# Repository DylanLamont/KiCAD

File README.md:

# KiCAD
Repo to save KiCAD Projects

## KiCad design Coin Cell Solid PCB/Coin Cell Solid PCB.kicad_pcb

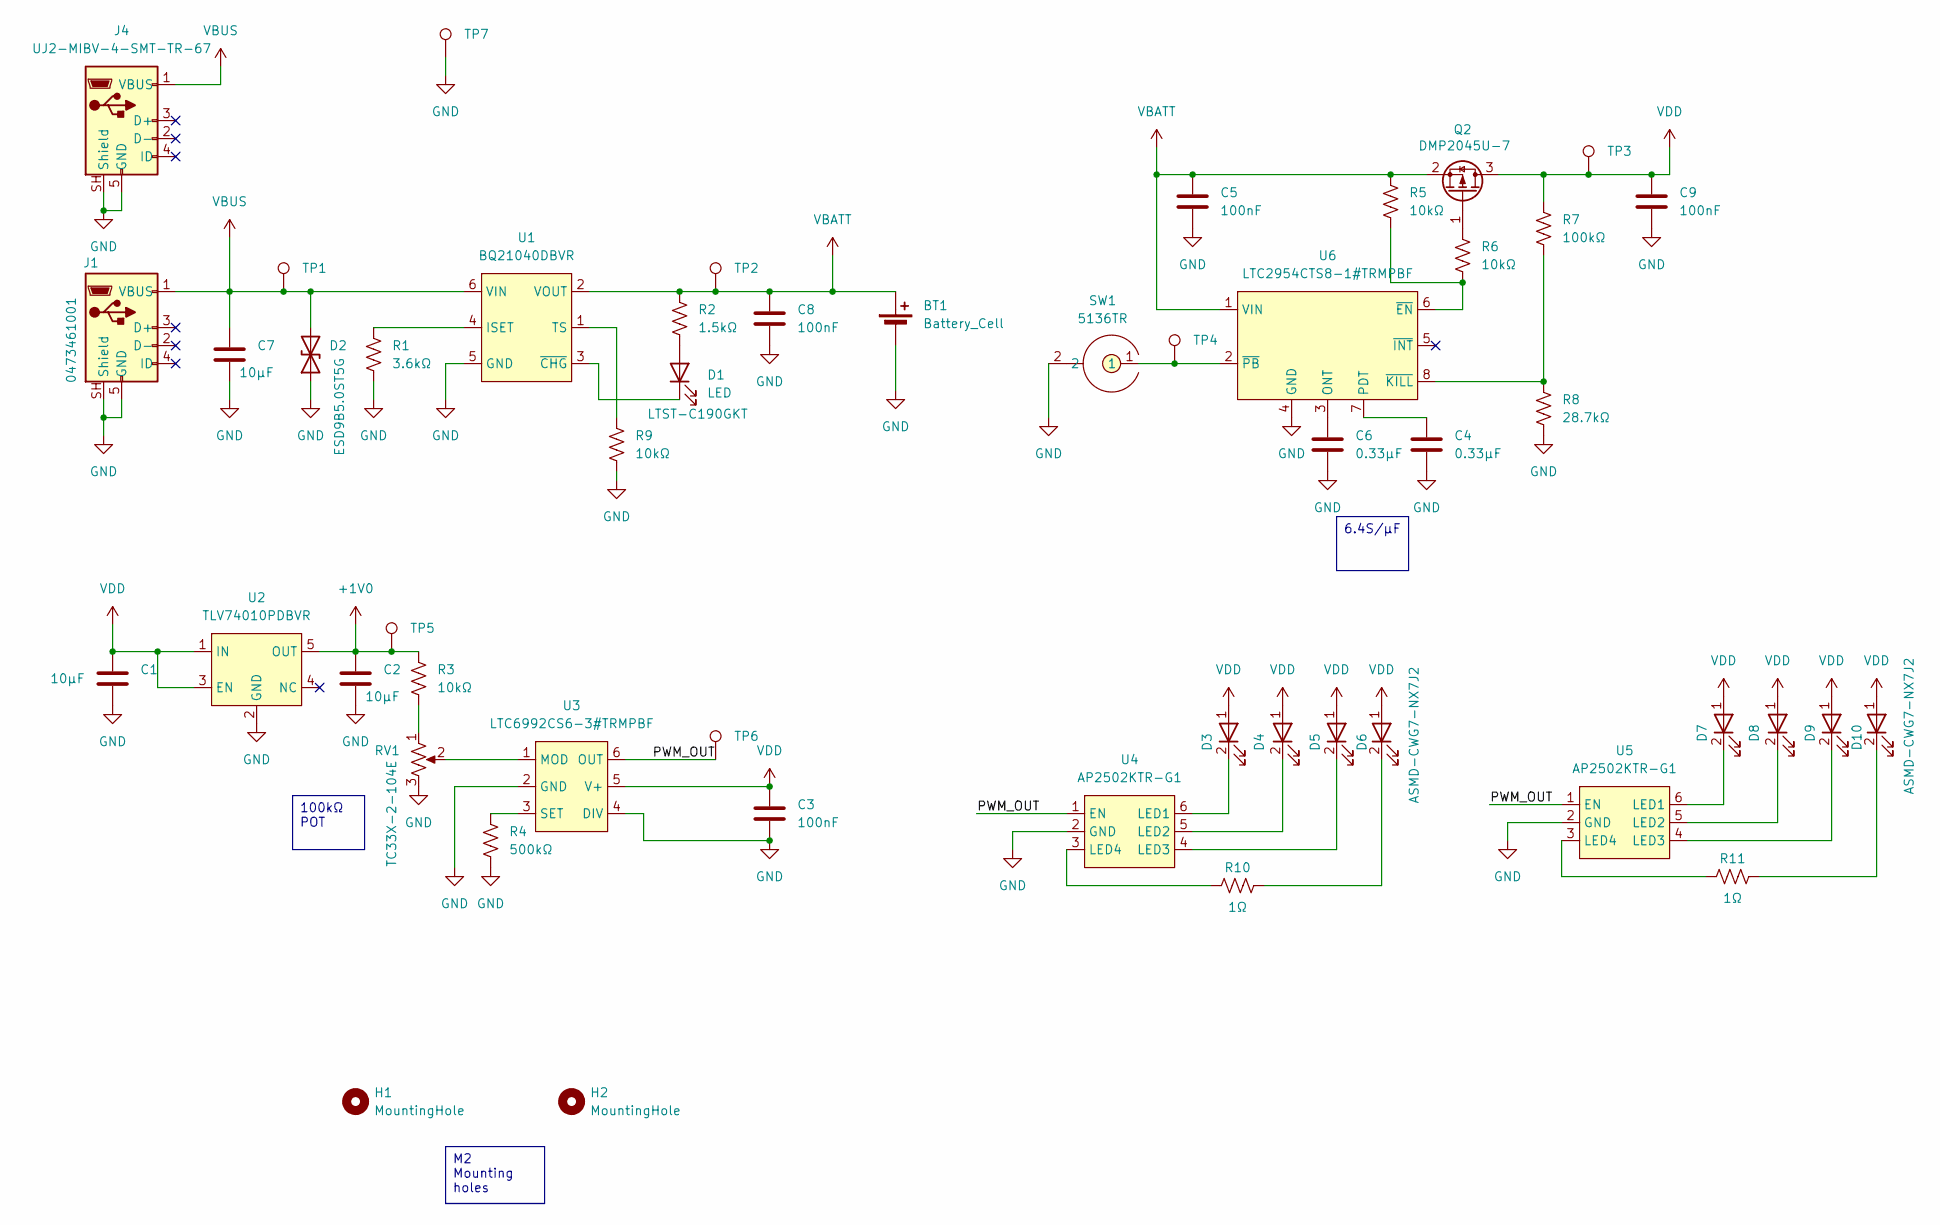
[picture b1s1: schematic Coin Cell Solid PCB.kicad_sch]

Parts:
BT1: Battery_Cell; Keystone_3047
C1, C2, C7: 10µF; C_0603_1608Metric
C3, C5, C8, C9: 100nF; C_0603_1608Metric
C4, C6: 0.33µF; C_0603_1608Metric
D1: LED; LED_0603_1608Metric; MFG PN LTST-C190GKT
D2: D_TVS; D_SOD-923; MFG PN ESD9B5.0ST5G
D3, D4, D5, D6, D7, D8, D9, D10: ASMD-CWG7-NX7J2; BroadCom_ASMD-CWG7-NX7J2
H1, H2: MountingHole; MountingHole_2.2mm_M2_ISO14580
J1: 0473461001; Molex_0473461001
J4: UJ2-MIBV-4-SMT-TR-67; SameSky_UJ2-MIBV-4-SMT-TR-67
Q2: Q_PMOS_GSD; SOT-23; MFG PN DMP2045U-7
R1: 3.6kΩ; R_0603_1608Metric_Pad0.98x0.95mm_HandSolder
R2: 1.5kΩ; R_0603_1608Metric_Pad0.98x0.95mm_HandSolder
R3, R5, R6, R9: 10kΩ; R_0603_1608Metric_Pad0.98x0.95mm_HandSolder
R4: 500kΩ; R_0603_1608Metric_Pad0.98x0.95mm_HandSolder
R7: 100kΩ; R_0603_1608Metric_Pad0.98x0.95mm_HandSolder
R8: 28.7kΩ; R_0603_1608Metric_Pad0.98x0.95mm_HandSolder
R10, R11: 1Ω; R_0603_1608Metric_Pad0.98x0.95mm_HandSolder
RV1: R_Potentiometer_US; Bourns_TC33X-2-104E; MFG PN TC33X-2-104E
SW1: 5136TR; Keystone_5136TR
TP1, TP2, TP3, TP4, TP5, TP6: TestPoint; TestPoint_Pad_D1.0mm
TP7: TestPoint; Harwin_S2761-46R
U1: BQ21040DBVR; SOT-23-6
U2: TLV74010PDBVR; SOT-23-5_HandSoldering
U3: LTC6992CS6-3#TRMPBF; TSOT-23-6
U4, U5: AP2502KTR-G1; SOT-23-6
U6: LTC2954CTS8-1#TRMPBF; TSOT-23-8

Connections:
+1V0: C2.1, R3.1, TP5.1 (1_1), U2.5 (OUT)
/PWM_OUT: TP6.1 (1_1), U3.6 (OUT), U4.1 (EN), U5.1 (EN)
GND: BT1.2 (-), C1.2, C2.2, C3.2, C4.2, C5.2, C6.2, C7.2, C8.2, C9.2, D2.1 (A1), J1.5 (GND), J1.SH (Shield), J4.5 (GND), J4.SH (Shield), R1.2, R4.2, R8.2, R9.2, RV1.3, SW1.2, TP7.1 (1_1), U1.5 (GND), U2.2 (GND), U3.2 (GND), U3.4 (DIV), U4.2 (GND), U5.2 (GND), U6.4 (GND)
unnamed: D1.2 (A), R2.2
unnamed: D1.1 (K), U1.3 (~CHG)
unnamed: D6.2, R10.2
unnamed: D10.2, R11.2
unnamed: Q2.1 (G), R6.1
unnamed: R3.2, RV1.1
unnamed: R1.1, U1.4 (ISET)
unnamed: R9.1, U1.1 (TS)
unnamed: RV1.2, U3.1 (MOD)
unnamed: R4.1, U3.3 (SET)
unnamed: D3.2, U4.6 (LED1)
unnamed: D4.2, U4.5 (LED2)
unnamed: D5.2, U4.4 (LED3)
unnamed: R10.1, U4.3 (LED4)
unnamed: D7.2, U5.6 (LED1)
unnamed: D8.2, U5.5 (LED2)
unnamed: D9.2, U5.4 (LED3)
unnamed: R11.1, U5.3 (LED4)
unnamed: C6.1, U6.3 (ONT)
unnamed: C4.1, U6.7 (PDT)
unnamed: R5.2, R6.2, U6.6 (~EN)
unnamed: R7.2, R8.1, U6.8 (~KILL)
unnamed: SW1.1, TP4.1 (1_1), U6.2 (~PB)
VBATT: BT1.1 (+), C5.1, C8.1, Q2.2 (S), R2.1, R5.1, TP2.1 (1_1), U1.2 (VOUT), U6.1 (VIN)
VBUS: C7.1, D2.2 (A2), J1.1 (VBUS), J4.1 (VBUS), TP1.1 (1_1), U1.6 (VIN)
VDD: C1.1, C3.1, C9.1, D3.1, D4.1, D5.1, D6.1, D7.1, D8.1, D9.1, D10.1, Q2.3 (D), R7.1, TP3.1 (1_1), U2.1 (IN), U2.3 (EN), U3.5 (V+)

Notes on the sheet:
M2 Mounting holes
100kΩ POT
6.4S/µF

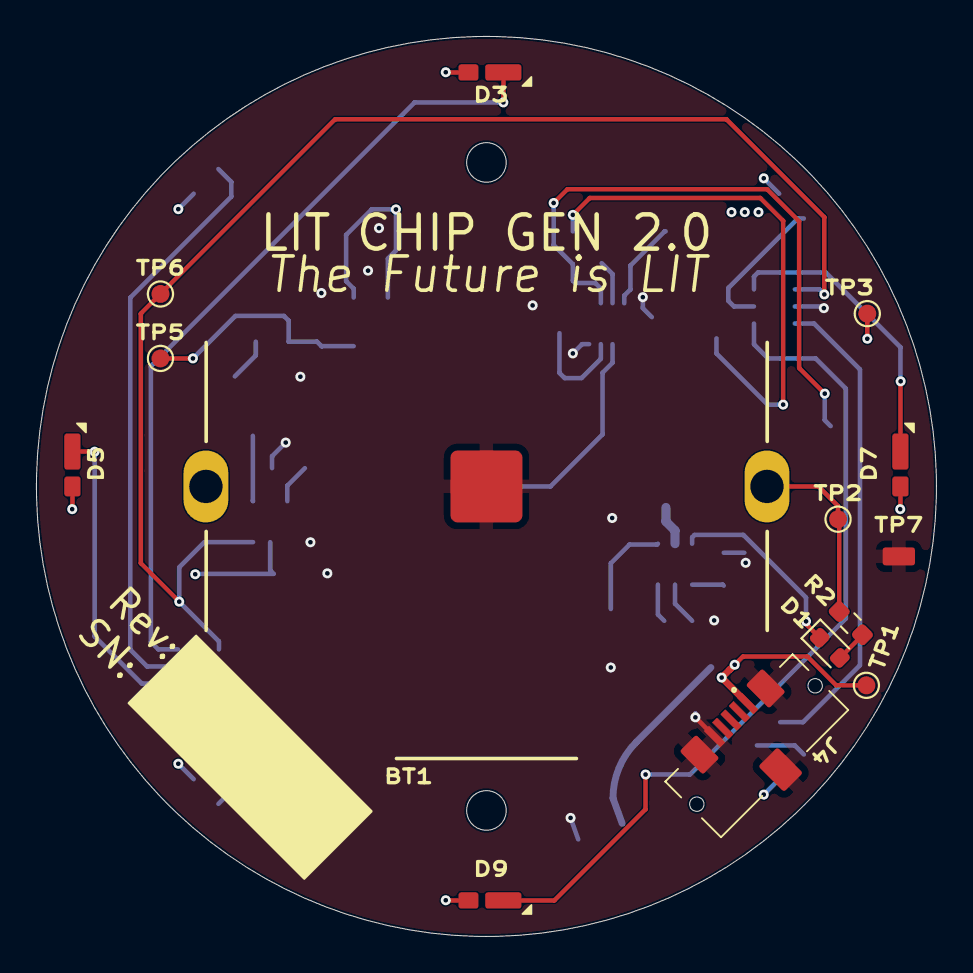
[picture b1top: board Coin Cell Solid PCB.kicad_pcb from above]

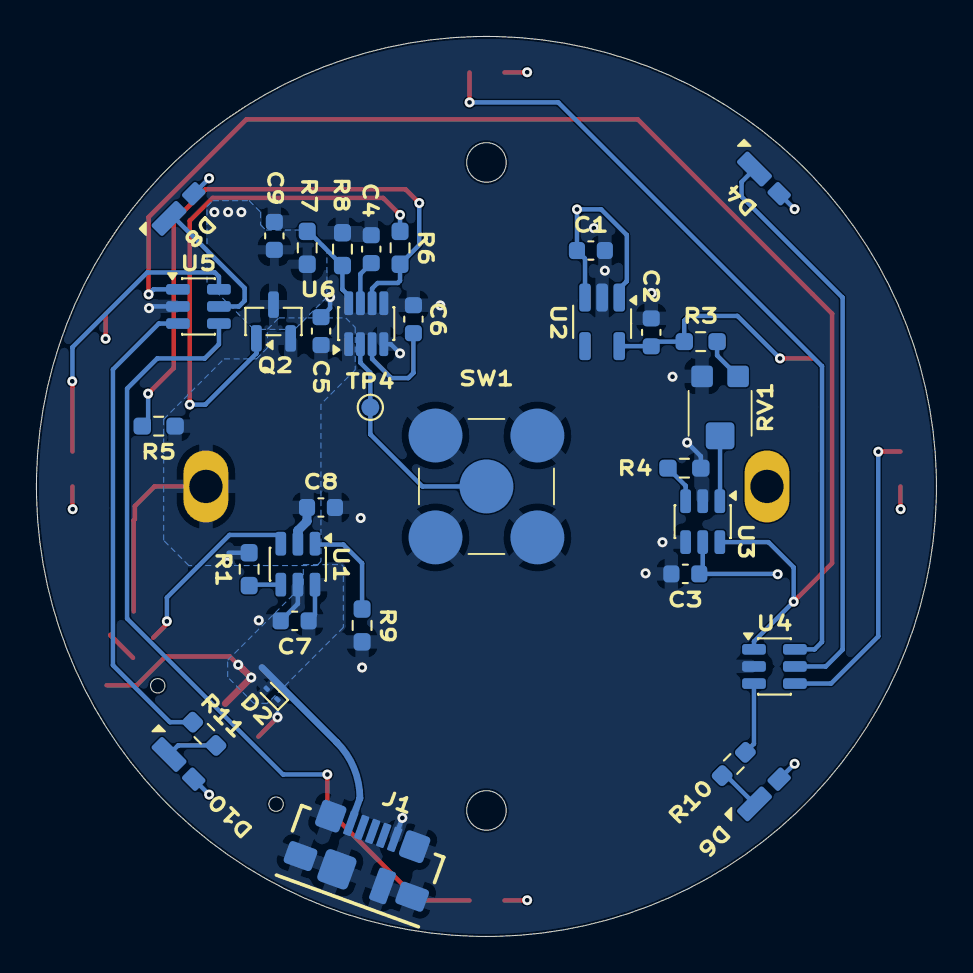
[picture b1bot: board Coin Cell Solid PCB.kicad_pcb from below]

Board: 4 copper layers, 50.0 x 50.0 mm, 51 parts (35 on the bottom side), 29 nets.
